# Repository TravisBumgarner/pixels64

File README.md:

# Pixels64

Pixels64 is an 8x8 grid of 64 individually addressable RGB LEDs using the WS2812B package. It’s powered by an ESP32 running CircuitPython with the neopixel library for control. It features a custom-designed circuit board and a 3D-printable housing.

(Need help? [Join the community](https://discord.com/invite/J8jwMxEEff)!)

This repository includes all the files needed to build the Pixel64 display.

- `cad` - 3D models for housing
- `circuit` - PCB diagram and schematic
- `code` - Code for showing various displays
- `web` - Browser control UI, pairs with `bluetooth-experimental` over Web Bluetooth
- `displays` Collection of displays to get inspired. [Check them out on Instagram](https://www.instagram.com/pixelssixtyfour/).

Additionally

- `my_displays` - What I am currently tinkering on to display.

The PCB is designed to be modular, allowing multiple boards to be combined in an N x M configuration for any display size.

## Setup

### Tools

- Wire cutters
- Soldering Iron

### Components

- esp32
- Three different colors of wire (Red, Black, Blue)
- White Filament
- Black Filament
- 4x pixel64 Boards
- 16x M3x6x4.2 Brass Knurled Nuts
- 16x M3x5 Metal Screws

### Quick Setup

1. Print `base-plate.stl` and `walls.stl` in black. Print `case.stl` in white.
1. Upload files in `jlcpcb` and order from JLCPCB
1. Cut wire to length
   - 3x 25mm Red
   - 3x 25mm Blue
   - 3x 25mm Black
   - 1x 12mm Red
   - 1x 12mm Blue
   - 1x 12mm Black
1. Solder boards together.
   - Blue (data) goes to the center pad. Red (power) to the square pad. Black (power) to the circle pad.
   - Solder the short wires to the `DataIn1` of the first PCB.
   - Solder the long wires from `Dataout1` to the `DataIn1` of the next PCB.
   - Repeat the previous step two more times.
1. Use a soldering iron to press fit the brass knurled nuts into the risers on the `base-plate.stl`.
1. Screw in the boards.
   - Note that all of the boards are oriented with `DataIn1` at the bottom.
   - The arrangement of boards is
   ```
   3 4
   1 2
   ```
1. Setup virtual environment `python -m venv venv` inside the code directory
1. Use virtual environment `source venv/bin/activate
1. Install dependencies `pip install -r requirements.txt`
1. Setup device
   1. Wipe device `esptool.py --chip esp32 --port [device] erase_flash`
   1. [Download MicroPython](https://micropython.org/download/ESP32_GENERIC/) - Your device may be different.
   1. `esptool.py --chip esp32 --port [device] --baud 460800 write_flash -z 0x1000 file.uf2`
1. Run `write.sh` script to upload files to device.
1. Pres the `en` button to shuffle the displays.

## Additional Notes

### CAD

#### Case

- The `case.stl` services as the "screen" of the pixel64. It can be challenging to get a clean print of such a size. You'll need very good first layer adhesion. An alternative here would be to make a case out of white acrylic instead or cover the walls with a white sheet of paper.

### Code

#### Useful commands

- Get a list of connected devices
  - `ls /dev/cu.* /dev/tty.*`
  - The desired device should look something like `tty.usbserial-0001`
- Get a terminal to esp32
  - `mpremote`
  - Note - you can't use the `print` statement while uploading code.
  - Be sure to setup your Python virtual environment before running `mpremote`.
  - `ctrl + ]` to exit
  - `ctrl + c` and `ctrl + d` to soft reboot and cycle through displays.
- Send file to esp32
  - `ampy --port /dev/tty.usbserial-0001 put boot.py`
  - If `put` fails, reconnect device.
  - Push button with "en" to launch code.
- Remove a file
  - `ampy --port /dev/tty.usbserial-0001 rm boot.py`
- List files
  - `ampy --port /dev/tty.usbserial-0001 ls`

### Circuit

#### NeoPixel Mapping

The LED circuit board I designed supports multiple configurations, meaning the default ordering of NeoPixels may not match the expected layout. For example, setting neopixel[0] = (255, 255, 255) won't necessarily light up the top-left LED.

This script cycles through each pixel one at a time, allowing you to determine the actual order. Once identified, we can remap the ordering. For example, the physical layout might be:

```
 3  2  1  0
 7  6  5  4
11 10  9  8
15 14 13 12
```

We can then transform it into a more intuitive sequence:

```
 0  1  2  3
 4  5  6  7
 8  9 10 11
12 13 14 15
```

This remapping ensures easier indexing and consistent control over the LEDs.

Take the following code and save it to `main.py`

```
import machine
import time
import neopixel

NEO_PIXEL_PIN = 13
NEO_PIXEL_COUNT = 64

neo_pin = machine.Pin(NEO_PIXEL_PIN, machine.Pin.OUT)
np = neopixel.NeoPixel(neo_pin, NEO_PIXEL_COUNT)

def set_pixel(i, r, g, b):
    np[i] = (r, g, b)
    np.write()

def main():
    while True:
        for i in range(64):
            set_pixel(i, 255, 0, 0)
            time.sleep_ms(2000)
            set_pixel(i, 0, 0, 0)

if __name__ == "__main__":
    main()

```

Upload the code to the esp32

```
ampy --port [replace with your device] put main.py
```

Place a sheet of paper over the LEDs and tape in place.

Press the `en` button on the esp32 to run the code.

You should see the LEDs light up in a red color.

Mark the first LED that lights up as `0` and complete until done.

Now, starting from the top left, write the numbers of the LEDs in a left to right top to bottom order in the config.py file, replacing the variable `LOOKUP`.

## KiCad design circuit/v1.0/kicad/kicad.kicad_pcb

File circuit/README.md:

# Circuit

Each version has two folders inside. 
- `kicad` contains the KiCad project files.
- `jlcpcb` contains the files sent to JLCPCB for order.

## V1.0 Initial PCB Design 

Specs
- Dimension: 100mm x 100mm
- Layers 2
- PCB Thickness: 1.6mm
- PCB Color: Black

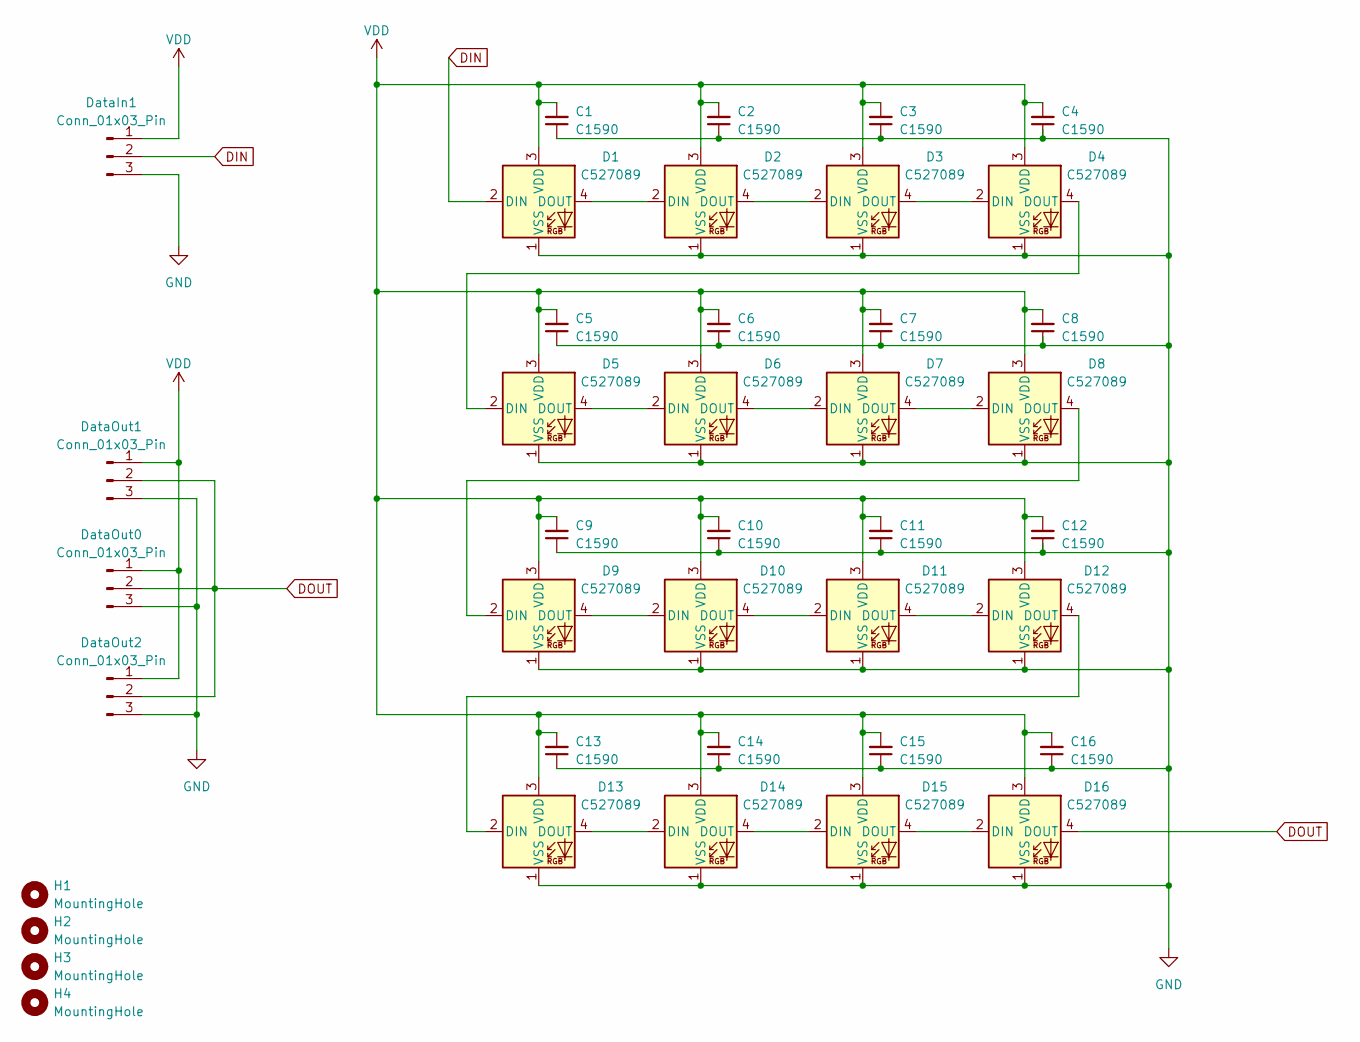
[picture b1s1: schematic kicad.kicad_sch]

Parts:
C1, C2, C3, C4, C5, C6, C7, C8, C9, C10, C11, C12, C13, C14, C15, C16: C1590; C_0805_2012Metric
D1, D2, D3, D4, D5, D6, D7, D8, D9, D10, D11, D12, D13, D14, D15, D16: C527089; LED_WS2812B-Mini_PLCC4_3.5x3.5mm
DataIn1: Conn_01x03_Pin; PinHeader_1x03_P2.54mm_Vertical
DataOut0, DataOut1, DataOut2: Conn_01x03_Pin; PinHeader_1x03_P2.54mm_Vertical
H1, H2, H3, H4: MountingHole; MountingHole_3.2mm_M3_DIN965_Pad

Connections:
DIN: D1.2 (DIN), DataIn1.2
DOUT: D16.4 (DOUT), DataOut0.2, DataOut1.2, DataOut2.2
GND: C1.1, C2.1, C3.1, C4.1, C5.1, C6.1, C7.1, C8.1, C9.1, C10.1, C11.1, C12.1, C13.1, C14.1, C15.1, C16.1, D1.1 (VSS), D2.1 (VSS), D3.1 (VSS), D4.1 (VSS), D5.1 (VSS), D6.1 (VSS), D7.1 (VSS), D8.1 (VSS), D9.1 (VSS), D10.1 (VSS), D11.1 (VSS), D12.1 (VSS), D13.1 (VSS), D14.1 (VSS), D15.1 (VSS), D16.1 (VSS), DataIn1.3, DataOut0.3, DataOut1.3, DataOut2.3
unnamed: D1.4 (DOUT), D2.2 (DIN)
unnamed: D2.4 (DOUT), D3.2 (DIN)
unnamed: D3.4 (DOUT), D4.2 (DIN)
unnamed: D4.4 (DOUT), D5.2 (DIN)
unnamed: D5.4 (DOUT), D6.2 (DIN)
unnamed: D6.4 (DOUT), D7.2 (DIN)
unnamed: D7.4 (DOUT), D8.2 (DIN)
unnamed: D8.4 (DOUT), D9.2 (DIN)
unnamed: D9.4 (DOUT), D10.2 (DIN)
unnamed: D10.4 (DOUT), D11.2 (DIN)
unnamed: D11.4 (DOUT), D12.2 (DIN)
unnamed: D12.4 (DOUT), D13.2 (DIN)
unnamed: D13.4 (DOUT), D14.2 (DIN)
unnamed: D14.4 (DOUT), D15.2 (DIN)
unnamed: D15.4 (DOUT), D16.2 (DIN)
VDD: C1.2, C2.2, C3.2, C4.2, C5.2, C6.2, C7.2, C8.2, C9.2, C10.2, C11.2, C12.2, C13.2, C14.2, C15.2, C16.2, D1.3 (VDD), D2.3 (VDD), D3.3 (VDD), D4.3 (VDD), D5.3 (VDD), D6.3 (VDD), D7.3 (VDD), D8.3 (VDD), D9.3 (VDD), D10.3 (VDD), D11.3 (VDD), D12.3 (VDD), D13.3 (VDD), D14.3 (VDD), D15.3 (VDD), D16.3 (VDD), DataIn1.1, DataOut0.1, DataOut1.1, DataOut2.1

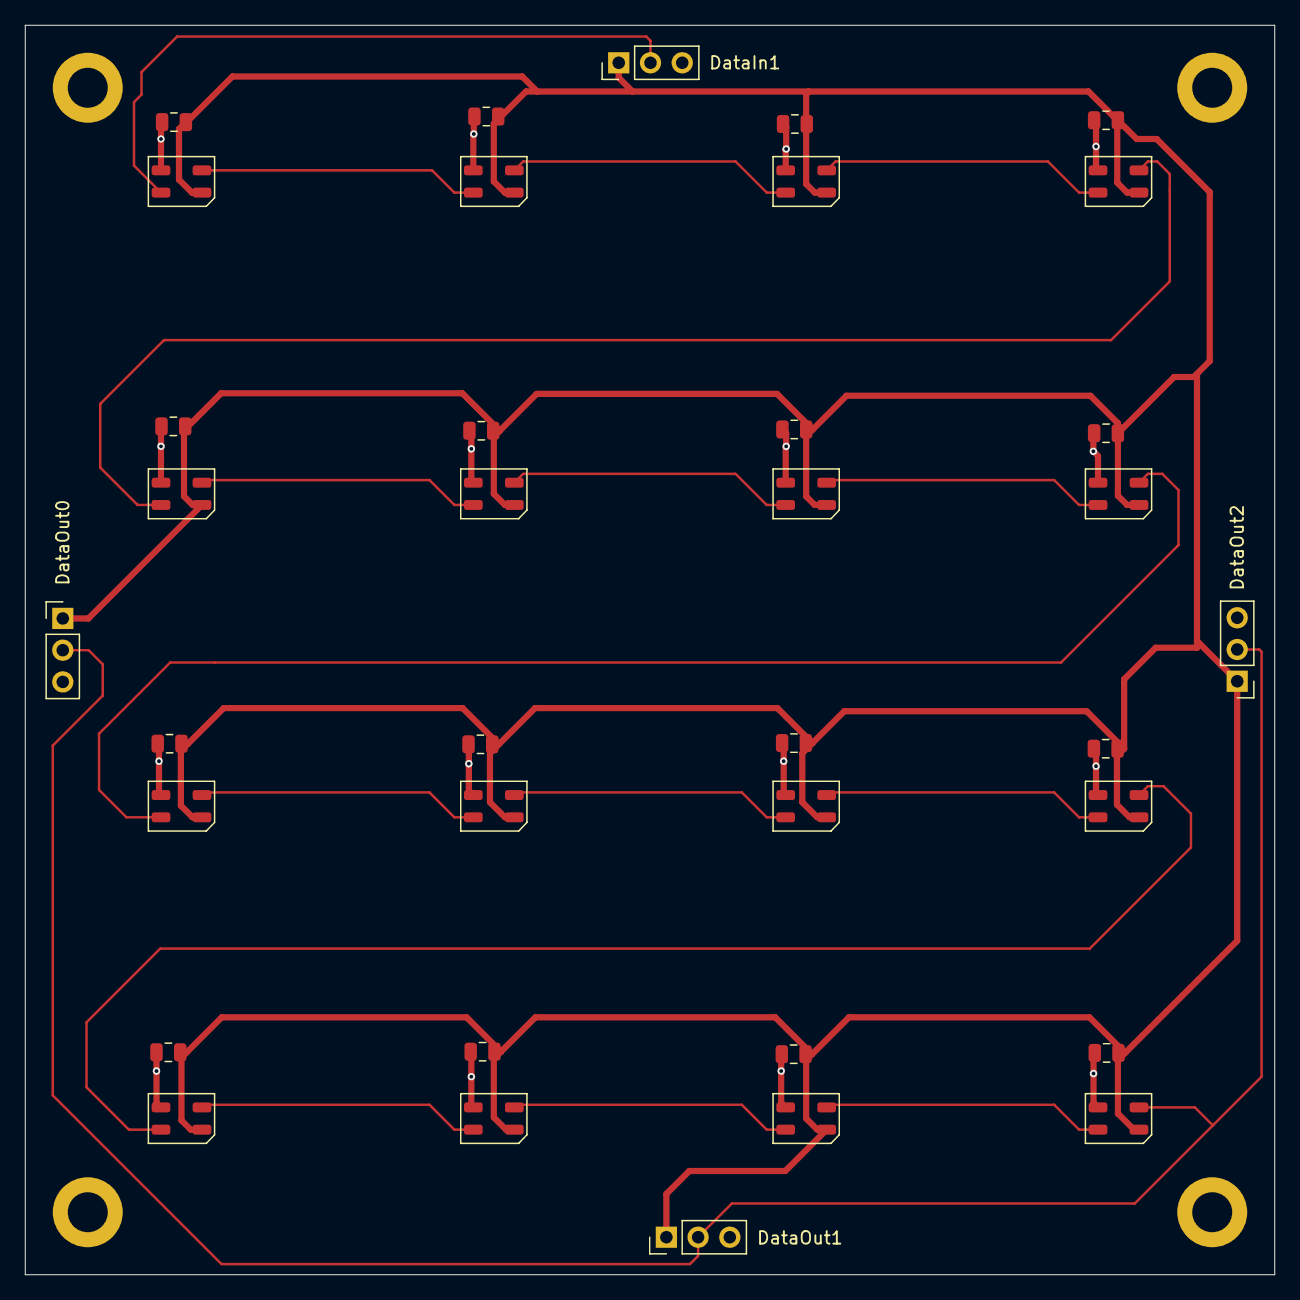
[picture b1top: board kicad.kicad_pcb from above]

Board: 2 copper layers, 100.0 x 100.0 mm, 40 parts (0 on the bottom side), 19 nets.

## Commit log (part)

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2025-01-25 starting point
2025-01-25 moved main
2025-01-25 added basic skeleton
2025-01-25 added button
2025-03-26 working again
2025-03-26 Initial Working Implementation (#1)
2025-03-26 bunch of docs
2025-03-26 better write script
2025-03-26 docs and log
2025-03-26 added random cycle on boot
2025-03-26 having fun with what AI gives me
2025-03-26 fun displays
2025-03-26 Documentation, Initial Displays (#2)
    * bunch of docs
    * better write script
    * docs and log
    * added random cycle on boot
    * having fun with what AI gives me
    * fun displays
2025-03-27 bunc of new files
2025-03-27 removed ds store
2025-03-27 dsstore is the worst
2025-03-27 Documentation, Initial Displays, PCB Files (#3)
    * bunch of docs
    * better write script
    * docs and log
    * added random cycle on boot
    * having fun with what AI gives me
    * fun displays
2025-03-27 added cad files
2025-03-27 better readmes and misc cleanup
2025-03-27 cleanup
2025-03-27 Full Documentation (#4)
    * added cad files
    * better readmes and misc cleanup
    * bunch of docs
    * cleanup
2025-03-27 first display
2025-03-27 First my_display (#5)
2025-03-27 done
2025-03-27 New Photo (#6)
2025-03-27 Update README.md (#7)
2025-03-31 new display
2025-04-01 looking good
2025-04-02 new links
2025-04-02 algorithm named
2025-04-02 New Display (#8)
    * new display
    * looking good
    * new links
    * algorithm named
2025-04-10 Seis Colores color palettes (#9)
    * new display
    * looking good
    * new links
    * algorithm named
    * done
2025-04-17 min reqs
2025-04-17 remaining bits
2025-04-17 Notes for new devices(#10)
    * min reqs
    * remaining bits
2025-09-27 hooeee progress
2025-09-27 pruning
2025-09-27 nice
2025-09-27 [SSP-859][SSP-858] Code Audit; Setup new Display (#11)
    * hooeee progress
    * pruning
    * nice
2025-09-27 whoops
2025-09-27 [SSP-859][SSP-858] Code Audit; Setup new Display Part 2 (#12)
    * hooeee progress
    * pruning
    * nice
    * whoops
2025-11-21 Christmas Update (#13)
2025-12-08 well that wraps up christmas lol
2025-12-08 Archive Christmas (#14)
    * done
    * well that wraps up christmas lol
2026-06-21 Replace wifi-experimental sandbox with bluetooth-experimental
    Drop the WiFi web-UI sandbox in favor of a Bluetooth-based approach.
    Removes wifi-experimental/ and adds bluetooth-experimental/ (BLE control
    with web UI). Also drops the now-obsolete wifi_config.py gitignore entry.
2026-06-21 Add README for bluetooth-experimental
    Document the BLE setup: firmware upload, the Web Bluetooth control UI,
    status indicator colors, and the binary command protocol.
